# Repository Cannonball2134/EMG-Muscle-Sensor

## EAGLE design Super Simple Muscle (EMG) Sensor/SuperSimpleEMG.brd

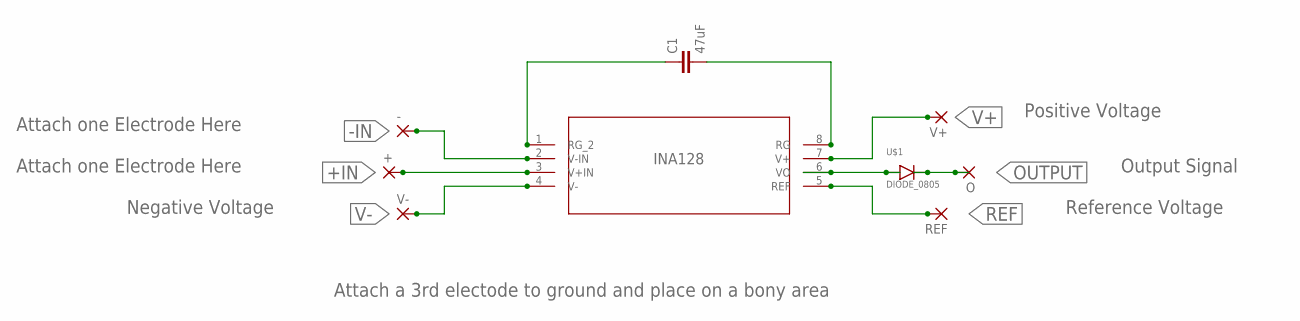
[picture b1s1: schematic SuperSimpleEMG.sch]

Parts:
+: 2,15/1,0
-: 2,15/1,0
C1: 47uF; 0805; MPN F980J476MSA
INA128: INA128_D_8; D8; MPN INA128U
O: 2,15/1,0
REF: 2,15/1,0
U$1: DIODE_0805
V+: 2,15/1,0
V-: 2,15/1,0

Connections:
+IN: +.1, INA128.3 (V+IN)
-IN: -.1, INA128.2 (V-IN)
unnamed: C1.1, INA128.1 (RG_2)
unnamed: C1.2, INA128.8 (RG)
unnamed: INA128.6 (VO), U$1.A
OUTPUT: O.1, U$1.C
REF: INA128.5 (REF), REF.1
V+: INA128.7 (V+), V+.1
V-: INA128.4 (V-), V-.1

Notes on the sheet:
Attach one Electrode Here
Attach a 3rd electode to ground and place on a bony area
Negative Voltage
Positive Voltage
Output Signal
Reference Voltage

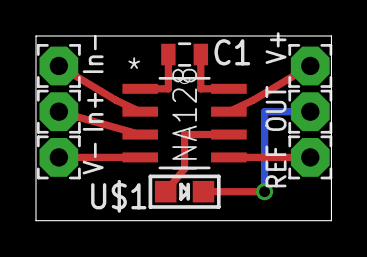
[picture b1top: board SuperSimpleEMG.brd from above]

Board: 2 copper layers, 16.4 x 10.3 mm, 9 parts (0 on the bottom side), 9 nets.

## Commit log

2015-12-18 :octocat: Added .gitattributes & .gitignore files
2015-12-18 Super Simple Muscle Sensor Design Files
    Eagle Design Files

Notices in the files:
parts and their libraries:
SparkFun-Passives: Licensing: CC v3.0 Share-Alike You are welcome to use this library for commercial purposes.
